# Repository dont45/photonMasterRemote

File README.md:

# photonMasterRemote
A photon Master Alarm system with any number of optional photon Remote nodes

See Wiki for lots more detail

Common source generates a master alarm node or a remote node.  
The master node is created by the #define PHOTON_MASTER line in parms.h.
A remote node is created by commenting out the master node #define , i.e. 
//#define PHOTON_MASTER which will result in a #define PHOTON_REMOTE
In addition, you must inclue the line #define REMOTE_SYSTEM_ID 1
The id number must be 1 or greater.  The id of the master node must be 0.

The master my have any number of it's own sensors defined in writeTestConfiguration.
The master's representation of a remote sensor is defined with device.use set to
SUB_REMOTE_THERMOMETER or SUB_REMOTE_SENSOR.  
The actual sensor is defined in the remote with master_idx set to the index number 
in the master which represents the remote sensor.

Communication of the remote sensor status is done via a particle.publish string which represents
the state of all of the remote sensors, such as:
3@1@T@13:12:16@TEST DOOR:2:0.000000:3@OUTSIDE TEMP:3:89.937500:0$
The @ character separates the first four data fields (sequence,remote id, alert type, and time).
Data for each sensor follows, also separated by an @ character.
These fields are parsed by the class Parse.

Each sensor's data fields are separated by a : character.  They are Name,device index in master,
and sensor reading.  These data fields are also parsed by class Parse.

The remote node publishes 'remoteData' to the particle cloud, and the master node is subscribed
to this cloud data field.  The remote node performs a publish immediately upon any sensor being
tripped, and also periodically as an Information update on a specified schedule, set in
parms.h.  This allows for immediate response to an alarm condition and periodic read on the
master node of other less time-sensitive data such as a temperature probe.  Upon receipt of the
subscribed remoteData, the master device is update with the new sensor data, stored into the
device record as dev_reading, and the current time is stored into dev_last_read.

In my operational test system, the hardware for both master and remote can be identical, except
for the attached sensors.  The remote node may also be of any custom design, as required.  It
only needs to publish a properly formatted data string as 'remoteData'.

I have implemented and tested the following configurations:

Master alarm in my house with sensors to read house temperature, boiler temperature, water detector,
fire alarm detector, motion detector, and magnetic door closure detectors.  All of these sensors
are 1-wire devices, such as a DS2413, DS1820, etc.  Temperature sensors can be either a 1-wire
device such as a DS18B20 or an I2C attached device such as an MCP9808 precision thermometer.
All 1-wire devices are attached to the photon by use of an I2C to 1-wire interface chip, the DS2482.
My home alarm / monitor system also includes two remote nodes.  Both of these nodes are implemented
with identical physical hardware, my custom PCB manufacture by PCBway from my Eagle design files.
The two remote nodes are 1) a remote alarm installed in my storage shed with a door sensor and an 
MCP9808 reading outside temperature, and 2) a remote node installed in my garage with a door sensor
for each garage door, motion-detector to cover the garage area, and a door sensor on the entry door
to the house.   This was implemented as a remote node in order to eliminate physical wiring back to
the master alarm.

I have also tested two unusual remote nodes.  One a battery powered photon with an ultrasonic distance
measurement device to read the hone heating fuel tank level.  See class Tank.
The second remote node is an Particle Electron based node installed in my truck which reads ambient 
temperature using an MCP9808 sensor, and transmits alarms if the temperature exceeds the device
settings.  It also sends a periodic Informational message of worry Temp.  This is to protect
my dog from dangerous heat while being left in the truch for short periods of time.  Both of these
remote nodes function like any remote node.  They simply publish 'remoteData' which is processed
by the master alarm.  Me and my truck can be thousands of miles away from home, and my home master
alarm functions to handle these high-temperature alerts from my truck to my iPhone just like any other
alarm sensor.

The master alarm publishes some data but the principal communication
to the user is done using web hooks to send alerts to my iPhone via Pushover.  

I have designed an iPhone app which communicates to the master alarm node.  The iPhone app receives a
minimal amount of data from the master directly.  These include alarm state and the current temperature
from one selected probe.  I have it configured to report the outside temperature from the shed.

A large amount of detail of the alarm configuration and current state is available by selection from
a drop-down menu in the app.  The resulting data is pushed to the iPhone as an alert message.
The commands available in the drop-down are:
HLP Help lists the available commands
ABT About tells a little about the system including the version
TMP Displays the current reading of all Temperature Sensors
SET Set the Alarm system to Enabled
DIS Disable the Alarm System
ACK Acknowledge an alarm condition
HOU Set the number of hours between worry pages
LIS List  basic information about sensors
NAM Set the Name of a sensor
SEN Show all detail of a sensor
ACT Set a sensor to active
DEA Disable a sensor
MIN Set minimum value to trigger an alert
MAX Set maximum value to tirgger an alert

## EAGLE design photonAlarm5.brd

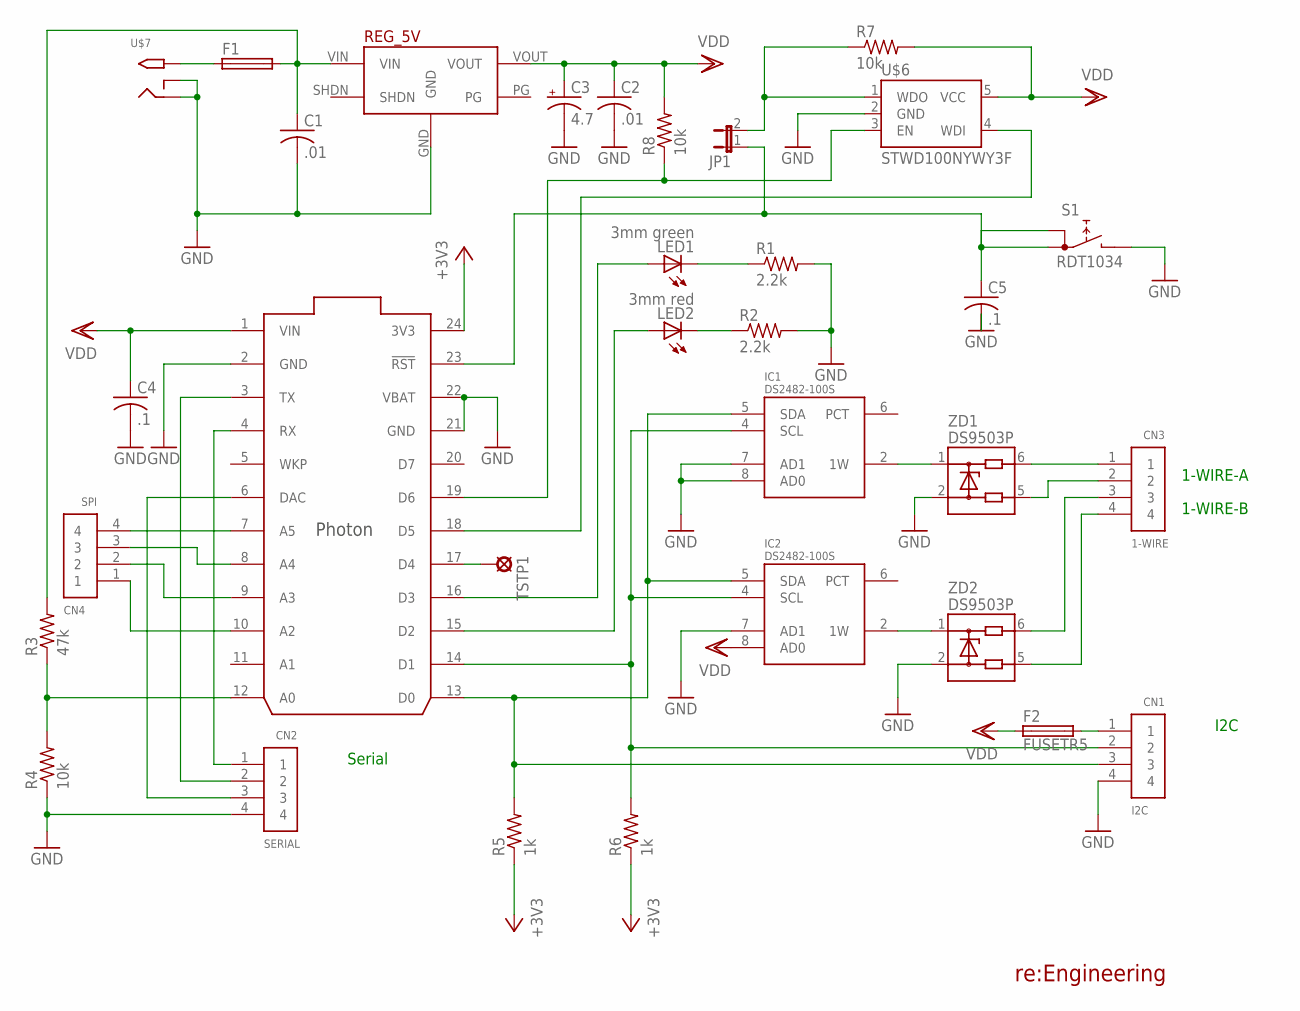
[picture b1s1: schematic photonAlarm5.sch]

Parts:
C1, C2: .01; C0805
C3: 4.7; E2,5-6E
C4, C5: .1; C0805
CN1: I2C; 1X04-BIG
CN2: SERIAL; 1X04-BIG
CN3: 1-WIRE; 1X04-BIG
CN4: SPI; 1X04-BIG
F1: PICOFUSE
F2: FUSETR5; TR5
IC1, IC2: DS2482-100S; SO08
JP1: JP1E; JP1
LED1: 3mm green; LED5MM
LED2: 3mm red; LED5MM
R1, R2: 2.2k; R1206
R3: 47k; R1206
R4, R7, R8: 10k; R1206
R5, R6: 1k; R1206
REG_5V: 5V_D24V10FAD24V10F5MIR; 5V_D24V10F5
S1: RDT1034
TSTP1: LSP10
U$1: PHOTON_WITH_HEADERS; PHOTON
U$6: STWD100NYWY3F; SOT23-5
U$7: 2.1MMJACKSMT; DCJACK_2MM_SMT
ZD1, ZD2: DS9503P; TSOC6

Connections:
+3V3: R5.1, R6.1, U$1.24 (3V3)
GND: C1.2, C2.2, C3.-, C4.2, C5.2, CN1.4, CN2.4, IC1.3 (GND), IC1.7 (AD1), IC1.8 (AD0), IC2.3 (GND), IC2.7 (AD1), R1.2, R2.2, R4.1, REG_5V.GND, S1.B, U$1.2 (GND), U$1.21 (GND), U$1.22 (VBAT), U$6.2 (GND), U$7.GND (RING), U$7.GNDBREAK (RING_SW), ZD1.2, ZD2.2
unnamed: TSTP1.MP, U$1.17 (D4)
unnamed: CN1.2, IC1.4 (SCL), IC2.4 (SCL), R6.2, U$1.14 (D1)
unnamed: LED1.K (C), R1.1
unnamed: LED2.K (C), R2.1
unnamed: LED1.A, U$1.16 (D3)
unnamed: LED2.A, U$1.15 (D2)
unnamed: CN1.3, IC1.5 (SDA), IC2.5 (SDA), R5.2, U$1.13 (D0)
unnamed: IC1.2 (1W), ZD1.1
unnamed: R3.1, R4.2, U$1.12 (A0)
unnamed: IC2.2 (1W), ZD2.1
unnamed: CN3.3, ZD2.6
unnamed: CN3.4, ZD2.5
unnamed: CN3.2, ZD1.5
unnamed: CN3.1, ZD1.6
unnamed: CN2.1, U$1.4 (RX)
unnamed: CN2.2, U$1.3 (TX)
unnamed: CN2.3, U$1.6 (DAC)
unnamed: U$1.18 (D5), U$6.4 (WDI)
unnamed: R8.1, U$1.19 (D6), U$6.3 (EN)
unnamed: CN1.1, F2.2
unnamed: CN4.4, U$1.7 (A5)
unnamed: CN4.3, U$1.8 (A4)
unnamed: F1.1, U$7.PWR2 (TIP)
unnamed: CN4.2, U$1.9 (A3)
unnamed: CN4.1, U$1.10 (A2)
unnamed: JP1.2, R7.1, U$6.1 (WDO)
RST: C5.1, JP1.1, S1.A, S1.A1, U$1.23 (!RST)
VDD: C2.1, C3.+, C4.1, F2.1, IC1.1 (VDD), IC2.1 (VDD), IC2.8 (AD0), R7.2, R8.2, REG_5V.VOUT, U$1.1 (VIN), U$6.5 (VCC)
VIN: C1.1, F1.2, R3.2, REG_5V.VIN

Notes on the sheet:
I2C
1-WIRE-A
re:Engineering
1-WIRE-B
Serial

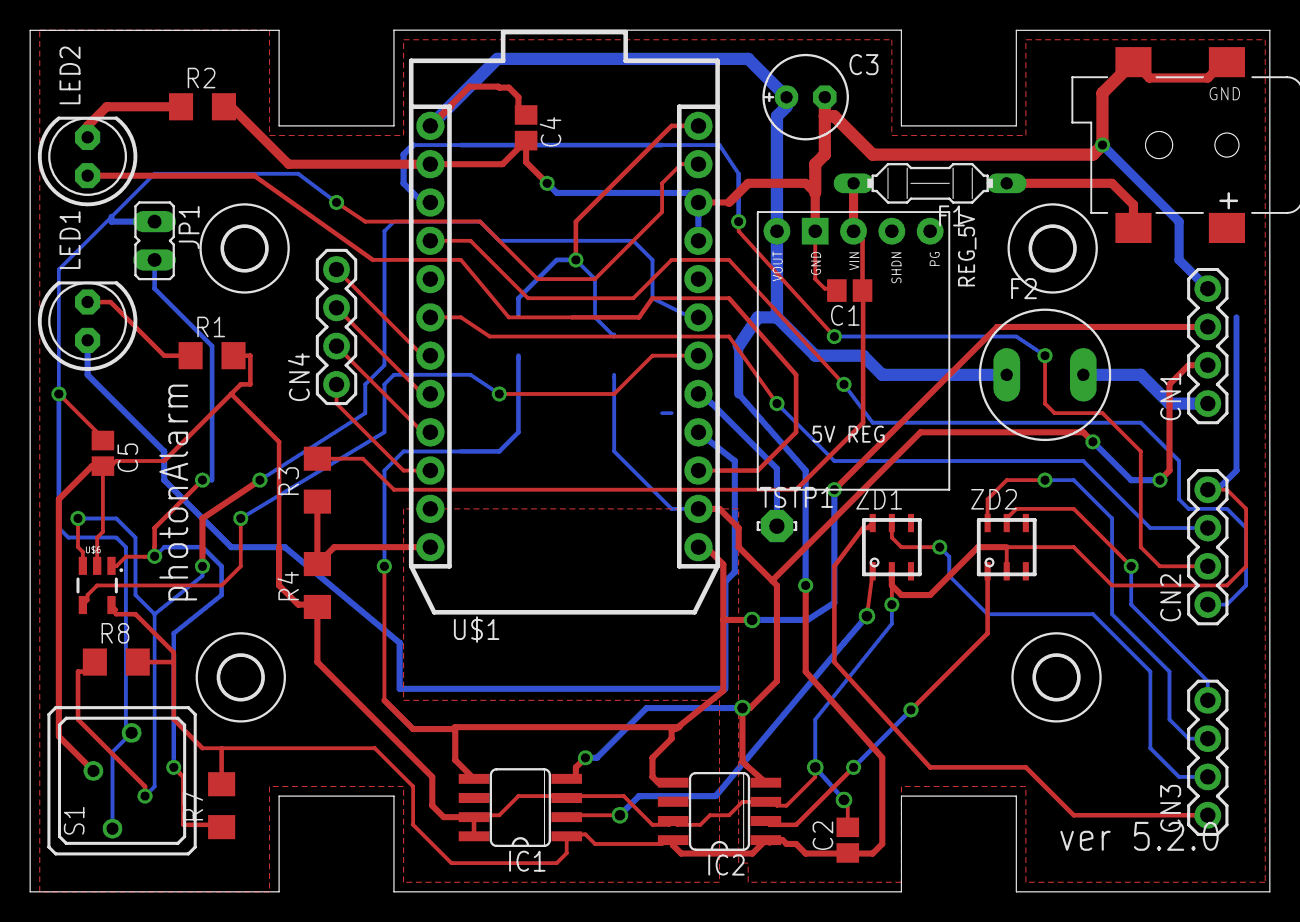
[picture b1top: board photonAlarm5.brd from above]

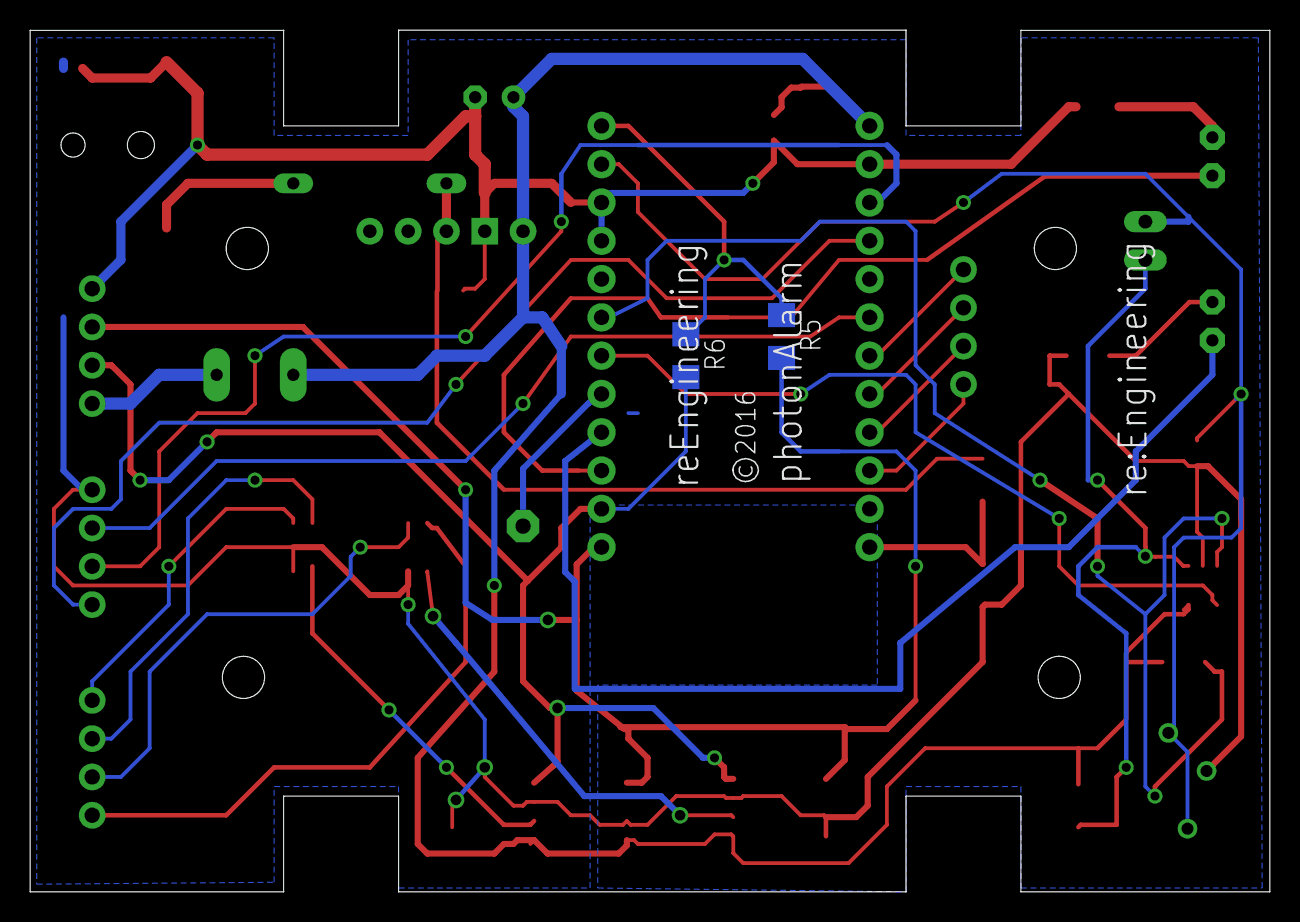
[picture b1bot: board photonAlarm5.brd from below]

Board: 2 copper layers, 82.2 x 57.1 mm, 36 parts (2 on the bottom side), 31 nets.

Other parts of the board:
U$2, U$3, U$4, U$5: 2,8

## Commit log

2016-08-30 Create master branch via GitHub
2016-09-08 Revisions and Enhancements
    Added Event Handling to class Alarm
    Rewrite of setState, setting alarm state as a state machine
2016-09-20 Create \Hardware
2016-09-20 Create xxxx
2022-07-04 Add files via upload
    Update: V7.0.1 03-Jul-2022

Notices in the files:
photonAlarm5.brd:
©2016
